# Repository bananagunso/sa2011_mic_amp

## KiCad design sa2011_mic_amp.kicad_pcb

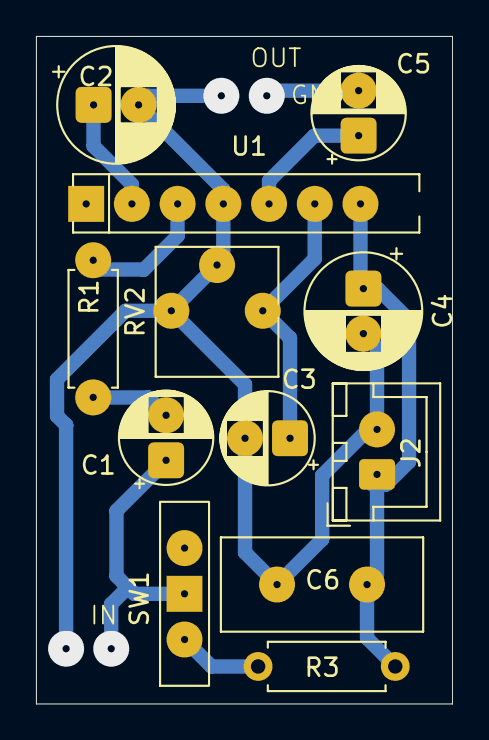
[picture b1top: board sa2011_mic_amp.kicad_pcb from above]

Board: 2 copper layers, 23.1 x 37.1 mm, 12 parts (0 on the bottom side), 9 nets.

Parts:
C1: BP25v4.7u; CP_Radial_D5.0mm_P2.50mm
C2, C4: 25v47u; CP_Radial_D6.3mm_P2.50mm
C3, C5: 25v10u; CP_Radial_D5.0mm_P2.50mm
C6: 0.1u; C_Disc_D11.0mm_W5.0mm_P5.00mm
J2: Conn_01x02_Pin; JST_XH_B2B-XH-A_1x02_P2.50mm_Vertical
R1: 2.2k; R_Axial_DIN0207_L6.3mm_D2.5mm_P7.62mm_Horizontal
R3: 4.7k; R_Axial_DIN0207_L6.3mm_D2.5mm_P7.62mm_Horizontal
RV2: 1M; Potentiometer_Vishay_T73YP_Vertical
SW1: SW_SPST; SW_Slide-03_Wuerth-WS-SLTV_10x2.5x6.4_P2.54mm
U1: SA2011; SIP-7_19x3mm_P2.54mm

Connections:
GND: C2.2, C3.2, C4.2, C6.1, J2.2, RV2.2, RV2.3, U1.4 (GND)
unnamed: C1.2, R1.2
unnamed: C1.1, SW1.1 (A)
unnamed: R3.2, SW1.2 (B)
unnamed: C3.1, RV2.1, U1.6 (DETOUT)
unnamed: R1.1, U1.3 (IN)
unnamed: C2.1, U1.2 (IN-)
unnamed: C5.1, U1.5 (OUT)
VCC 4～14v: C4.1, C6.2, J2.1, R3.1, U1.7 (VCC)

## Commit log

2025-11-19 デジットのキットの回路
2025-11-19 ALCを可変抵抗に、EMCとの切り替えスイッチをつけて配置
2025-11-20 パッドの大きさを2に
2025-11-23 縦長に配置を変更
2025-11-24 パッド修正、ベタ追加
2025-11-24 ベタを修正
2025-11-26 配置を修正
